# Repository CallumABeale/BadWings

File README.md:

# BadWings
Custom keyboard repo for my BadWings design (yes that's a glitch mob reference)

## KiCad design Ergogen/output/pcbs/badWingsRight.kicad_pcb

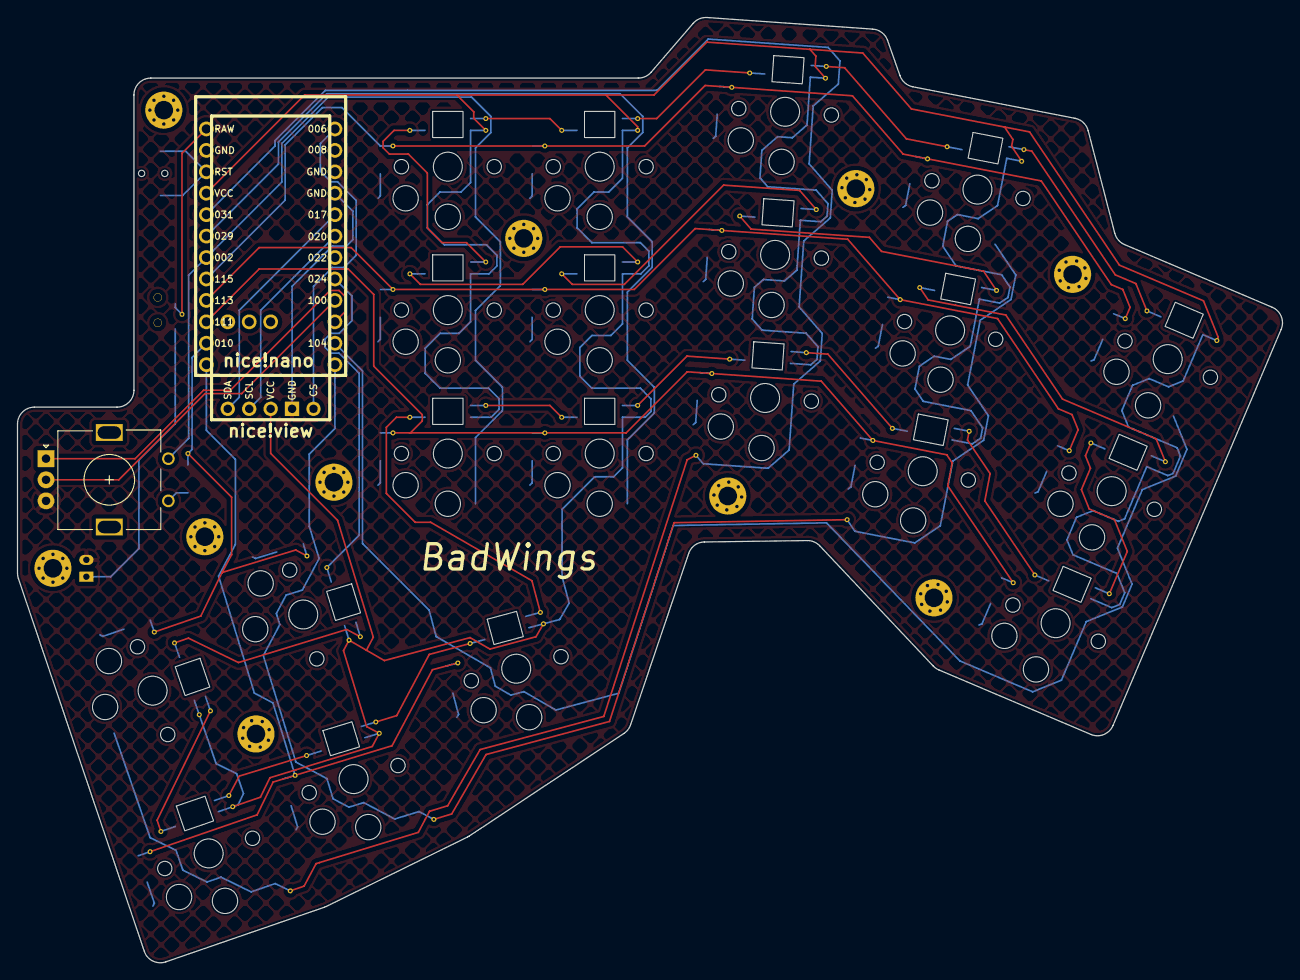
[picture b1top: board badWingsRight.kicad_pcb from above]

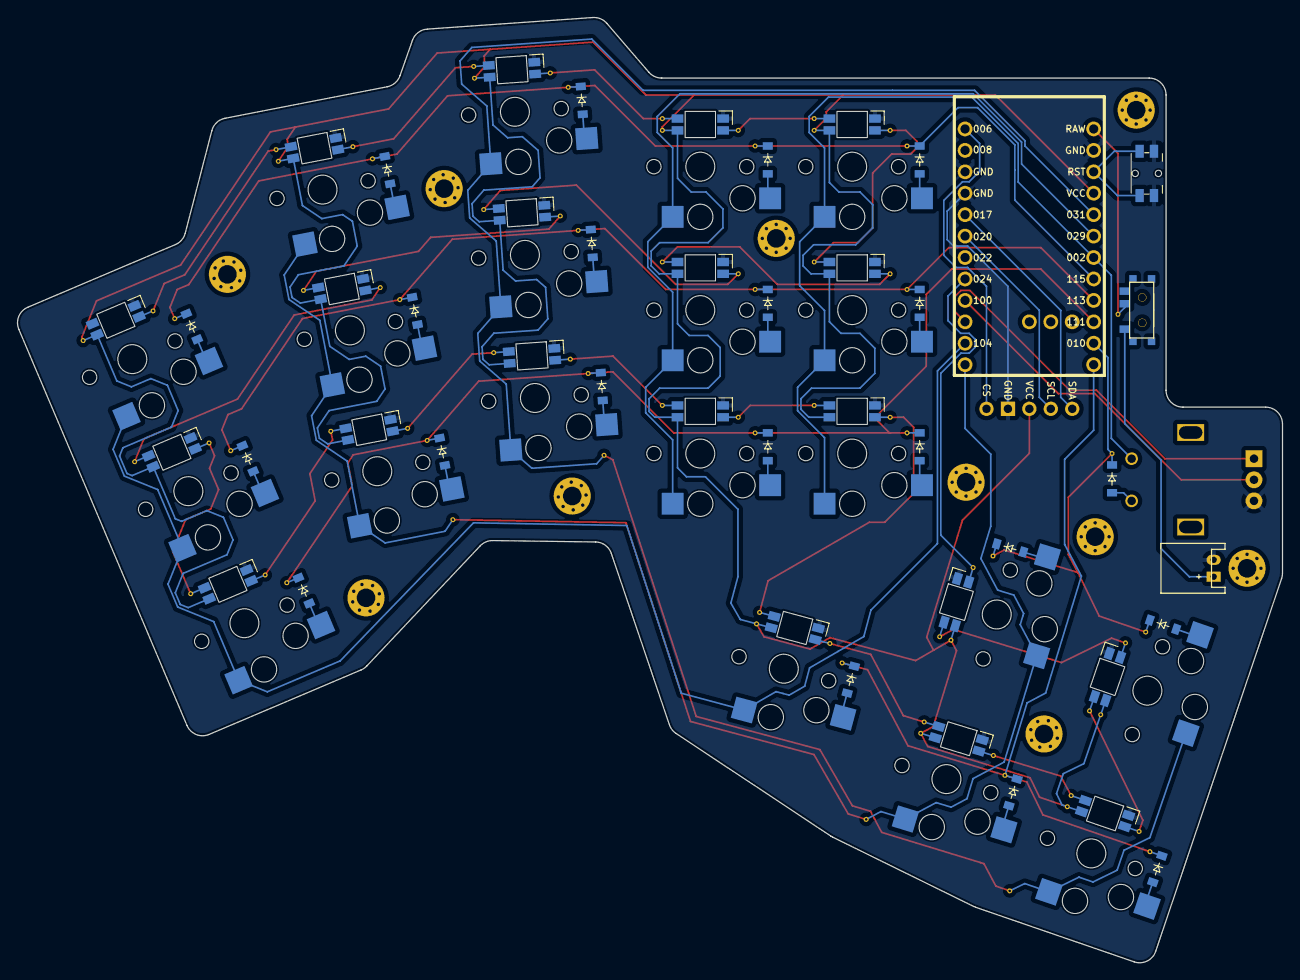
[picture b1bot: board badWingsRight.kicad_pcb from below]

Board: 2 copper layers, 149.9 x 112.0 mm, 77 parts (42 on the bottom side), 61 nets.

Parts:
B1: Panasonic_EVQPUL_EVQPUC
D1, D2, D3, D4, D5, D6, D7, D8, D9, D10, D11, D12, D13, D14, D15, D16, D17, D18, D19, D20, D21: diode_tht_sod123
JST1: JST_PH_S2B-PH-K_02x2.00mm_Angled
LED1, LED2, LED3, LED4, LED5, LED6, LED7, LED8, LED9, LED10, LED11, LED12, LED13, LED14, LED15, LED16, LED17, LED18, LED19, LED20: led_SK6812mini-e (per-keysingle-side)
MCU1: nice_nano
ROT1: rotary_encoder
S1, S2, S3, S4, S5, S6, S7, S8, S9, S10, S11, S12, S13, S14, S15, S16, S17, S18, S19, S20: PG1350
T1: SPDT_C128955
_76, _77, _78, _79, _80, _81, _82, _83, _84, _85: MountingHole_2.2mm_M2_Pad_Via
niceView1: niceView; niceView_headers

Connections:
GND: B1.1, JST1.2, LED1.3, LED2.3, LED3.3, LED4.3, LED5.3, LED6.3, LED7.3, LED8.3, LED9.3, LED10.3, LED11.3, LED12.3, LED13.3, LED14.3, LED15.3, LED16.3, LED17.3, LED18.3, LED19.3, LED20.3, MCU1.3, MCU1.4, MCU1.23, ROT1.B, niceView1.2
LED1: LED18.2, LED20.4
LED2: LED19.4, LED20.2
LED3: LED17.4, LED19.2
LED4: LED16.4, LED17.2
LED5: LED13.4, LED16.2
LED6: LED10.4, LED13.2
LED7: LED7.4, LED10.2
LED8: LED4.4, LED7.2
LED9: LED1.4, LED4.2
LED10: LED1.2, LED2.4
LED11: LED2.2, LED5.4
LED12: LED5.2, LED8.4
LED13: LED8.2, LED11.4
LED14: LED11.2, LED14.4
LED15: LED14.2, LED15.4
LED16: LED12.4, LED15.2
LED17: LED9.4, LED12.2
LED18: LED6.4, LED9.2
LED19: LED3.4, LED6.2
P002: MCU1.18, ROT1.1, S13.1, S14.1, S15.1
P006: MCU1.1, niceView1.1
P009: D16.1, D17.1, D19.1, MCU1.13
P010: D18.1, D20.1, D21.1, MCU1.14
P011: MCU1.10, ROT1.A
P017: MCU1.5, niceView1.5
P020: MCU1.6, niceView1.4
P024: LED18.4, MCU1.8
P029: MCU1.19, S10.1, S11.1, S12.1
P031: MCU1.20, S7.1, S8.1, S9.1, S19.1, S20.1
P100: MCU1.9, ROT1.C
P104: MCU1.11, S1.1, S2.1, S3.1, S16.1
P106: MCU1.12, S4.1, S5.1, S6.1, S17.1, S18.1
P111: D1.1, D4.1, D7.1, D10.1, D13.1, MCU1.15
P113: D2.1, D5.1, D8.1, D11.1, D14.1, MCU1.16
P115: D3.1, D6.1, D9.1, D12.1, D15.1, MCU1.17
RAW: MCU1.24, T1.2
RST: B1.2, MCU1.22
VCC: LED1.1, LED2.1, LED3.1, LED4.1, LED5.1, LED6.1, LED7.1, LED8.1, LED9.1, LED10.1, LED11.1, LED12.1, LED13.1, LED14.1, LED15.1, LED16.1, LED17.1, LED18.1, LED19.1, LED20.1, MCU1.21, niceView1.3
endiode: D21.2, ROT1.2
mirror_center_bottom: D17.2, S17.2
mirror_center_top: D18.2, S18.2
mirror_index_bottom: D10.2, S10.2
mirror_index_home: D11.2, S11.2
mirror_index_top: D12.2, S12.2
mirror_inner_bottom: D13.2, S13.2
mirror_inner_home: D14.2, S14.2
mirror_inner_top: D15.2, S15.2
mirror_left_bottom: D16.2, S16.2
mirror_middle_bottom: D7.2, S7.2
mirror_middle_home: D8.2, S8.2
mirror_middle_top: D9.2, S9.2
mirror_pinky_bottom: D1.2, S1.2
mirror_pinky_home: D2.2, S2.2
mirror_pinky_top: D3.2, S3.2
mirror_right_bottom: D19.2, S19.2
mirror_right_top: D20.2, S20.2
mirror_ring_bottom: D4.2, S4.2
mirror_ring_home: D5.2, S5.2
mirror_ring_top: D6.2, S6.2
pos: JST1.1, T1.1

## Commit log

2025-09-02 Left outline complete
2025-09-27 BadWings Progress
    Key layout design complete
    Outline complete
    PCB - WIP
2025-10-04 Added footprints
2025-10-04 Current state of ergogen config
    Need to swap some footprints to different versions for better layout
2025-10-09 Progress
    nice_nano side changed to back of board (because I want to see the text)
    jstph position changed
    encoder position changed
    mounting hole positions shifted to fit battery and new encoder position
2025-10-13 PCB design
    Left PCB design complete (pre sanity check)
2025-10-13 PCB Right
    Right side complete (pending sanity check)
2025-10-17 PCB update
    LED's routed differently to fix tracing conflicts
    Extra vias added to avoid trace conflicts
2025-10-18 Left board traced
2025-10-18 Fix right half diode direction
2025-10-18 Added git ignore
2025-11-02 Board design complete
2025-11-12 Cleanup & Cases
2025-11-14 Board v1.1 Complete
    Complete prior to assembly
    Case modifications could still be required
2025-11-14 Updated gitignore
2025-11-22 Updated config for v2 case
2025-11-25 V3 case update
    Interior standoff width increased
    Exterior standoff width increased
    Bottom battery wall lowered
    pwr/rst holes increased
    Legs + Rubber feet locations updated
2025-12-02 Add ZMK config repo as submodule
2025-12-02 Minor update to case dimensions for bottom wall
